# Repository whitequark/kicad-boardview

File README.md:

# KiCad to Boardview exporter

The _KiCad to Boardview exporter_ reads KiCad PCB layout files and writes _Boardview_ files. _Boardview_ is a set of file formats used in the industry for communicating important data about PCB in post-production stage, such as component, pin, and test point placement.

The _Boardview_ file formats do not typically have a specification or even a name. The _KiCad to Boardview_ exporter writes ".brd" files with ASCII _Boardview_ data. These files can be opened with MIT-licensed [OpenBoardView][].

[openboardview]: https://openboardview.org/

## Prerequisites

_KiCad to Boardview exporter_ uses the [pcbnew plugin interface][pcbplugin]. It requires KiCad 6 or later. It requires Python with KiCad libraries installed in the Python search path.

[pcbplugin]: https://dev-docs.kicad.org/en/apis-and-binding/pcbnew/

## Usage

Run the exporter as follows:

    ./pcbnew2boardview.py example/example.kicad_pcb example/example.brd

This will read the PCB layout from `example/example.kicad_pcb` and write it to `example/example.brd`.

## Examples

The _Boardview_ file for [Glasgow][] visualized with OpenBoardView looks like this, with the I2C SDA net selected:

For comparison, the PCB layout looks like this:

[glasgow]: https://github.com/whitequark/Glasgow

## Caveats

  * If the pin numbering on KiCad modules does not start with pin 1 and continue consecutively until last pin with an integer name, the pin numbering on the boardview will be wrong.
  * Similarly to the previous caveat, the format does not allow to represent pin names such as `PAD` (on QFN packages) or `A0` (on BGA packages) correctly. These will be assigned arbitrary (but consistent) numbers instead.
  * There is an unknown field in the ".brd" files, written as `0`. It is ignored by OpenBoardView, but might actually mean something.

## License

_KiCad to Boardview exporter_ is distributed under the terms of 0-clause BSD license.

See [LICENSE-0BSD](LICENSE-0BSD.txt) for details.

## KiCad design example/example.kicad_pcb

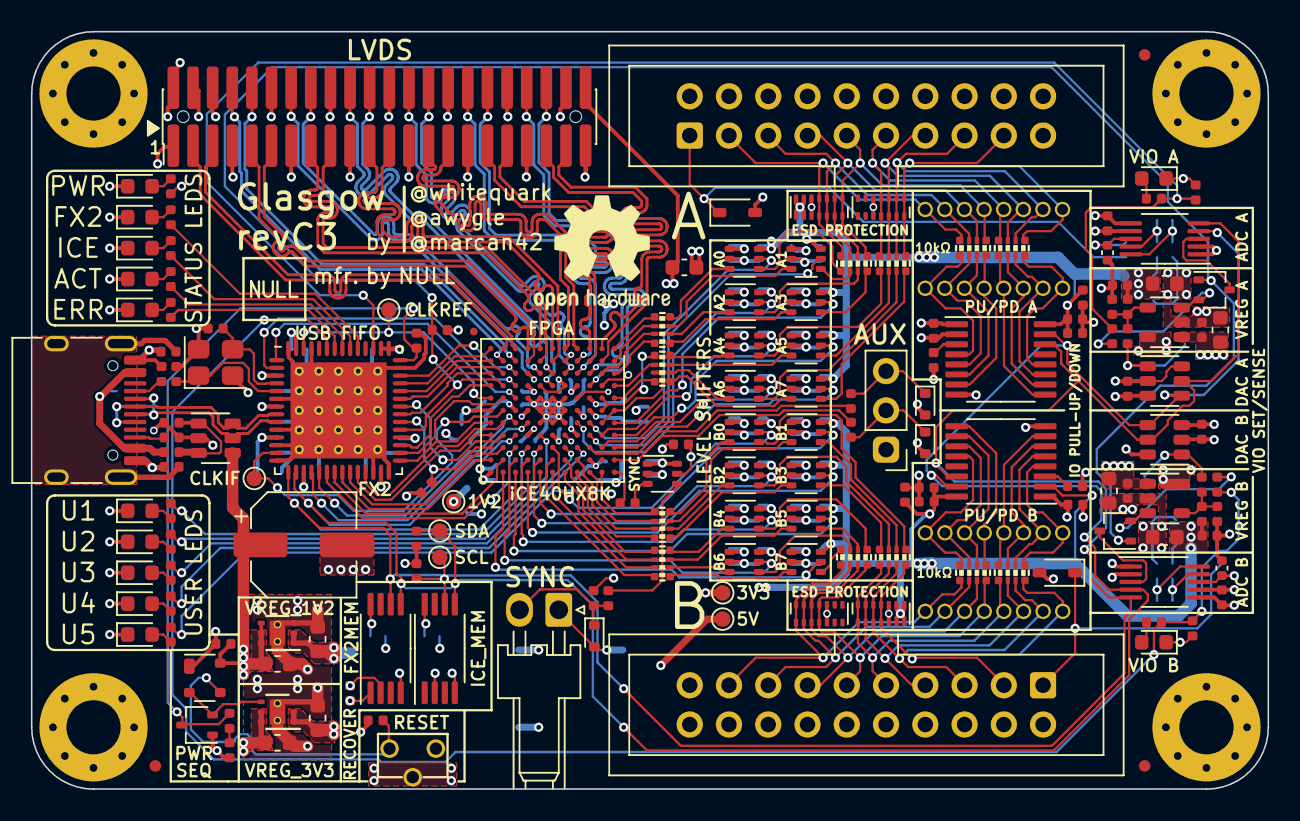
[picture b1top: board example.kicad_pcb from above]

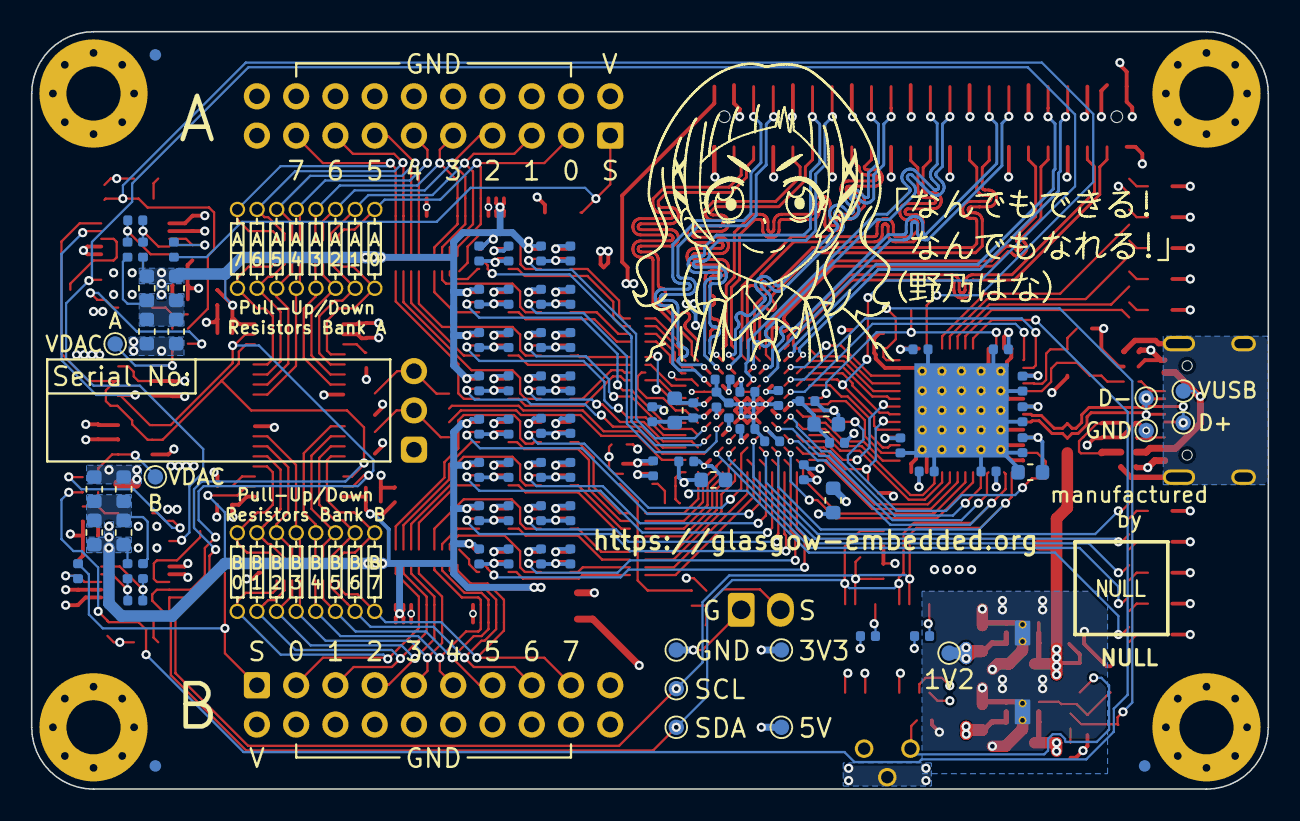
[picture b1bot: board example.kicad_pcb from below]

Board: 4 copper layers, 80.0 x 49.0 mm, 265 parts (93 on the bottom side), 226 nets.

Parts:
C1, C14, C19, C26, C27, C28, C31, C53, C76, C80, C82, C83, C86, C92: 4u7; C_0603_1608Metric
C2, C3, C4, C5, C6, C7, C8, C9, C10, C13, C15, C16, C17, C18, C20, C21, C22, C23, C24, C25, C29, C30, C32, C33, C34, C35, C36, C37, C38, C39, C40, C41, C42, C43, C44, C45, C46, C47, C48, C49, C50, C51, C52, C54, C55, C56, C57, C58, C59, C60, C61, C62, C63, C64, C65, C66, C67, C68, C69, C70, C71, C72, C73, C74, C75, C77, C78, C79, C81, C84, C85, C88, C89: u1; C_0402_1005Metric
C11, C12: 9p; C_0402_1005Metric
C87: 150u; CP_Elec_6.3x5.9
C90, C91: 1n 50V C0G; C_0402_1005Metric
D1, D14, D15: GRN; LED_0603_1608Metric
D2, D8: WHT; LED_0603_1608Metric
D3, D6, D10: BLU; LED_0603_1608Metric
D4: ORA; LED_0603_1608Metric
D5: RED; LED_0603_1608Metric
D7, D9: PNK; LED_0603_1608Metric
D11, D12, D13: ESD5Z5.0T1G; D_SOD-523
D16, D17: CDSOD323-T36S; D_SOD-323
D18, D19: BAT54CW; SOT-323_SC-70
D20, D21, D22, D23: SP3012-06UTG; UDFN-14_3.5x1.35mm_P0.5mm
D24: BAT54AW; SOT-323_SC-70
FB1: 600R, 0.5A; L_0402_1005Metric
FID1, FID2, FID3, FID4, FID5, FID6: Fiducial_0.75mm_Mask1.5mm
FID8: Fiducial_0.5mm_Dia_1mm_Outer
J1: USB_C_USB2.0; USB_C_Receptacle_HRO_TYPE-C-31-M-12
J2, J3: IDC-Header_2x10_P2.54mm; IDC-Header_2x10_P2.54mm_Vertical
J4: Conn_01x02; Molex_KK-254_1x02_P2.54mm_Horizontal
J5: PinHeader_2x22_P1.27mm; PinHeader_2x22_P1.27mm_Vertical__SMD
J6, J7, J8, J9: Conn_01x08; PinSocket_1x08_P1.27mm_Vertical_DNP
J10: AUX; PinHeader_1x03_P2.54mm_Vertical
MK1, MK2, MK3, MK4: Mounting_Hole_PAD; MountingHole_3.5mm_Pad_Via_CrtYd
NONO_HANA: MECHOKKU; nono_hana_lines
R1, R2, R10, R11, R13, R14, R20, R21, R22, R23, R41, R42, R57, R58: 2k2; R_0402_1005Metric
R3, R4, R5, R9, R17: 100k; R_0402_1005Metric
R6, R8, R50, R51: DNP; R_0603_1608Metric_DNP
R7, R56: 0R33; R_0603_1608Metric
R12, R18, R19, R26, R36, R37, R44, R55: 10k; R_0402_1005Metric
R15, R16: 1k; R_0402_1005Metric
R24, R25, R30, R54: 4R7; R_0402_1005Metric
R27, R33: 49k9; R_0402_1005Metric
R28, R34: 59k; R_0402_1005Metric
R29, R35: 24k3; R_0402_1005Metric
R31, R32: 100R; R_0402_1005Metric
R38, R39, R43, R45: 47R; R_0402_1005Metric
R40: DNP; R_0402_1005Metric_DNP
R46, R47: 20k; R_0402_1005Metric
R48, R49: 0R15; R_0603_1608Metric
R52, R53: 5k1; R_0402_1005Metric
R59, R60: 470; R_0402_1005Metric
RN1, RN2, RN3, RN4, RN7, RN8, RN9, RN10: 33R; R_Array_Convex_4x0402
RN5, RN6, RN11, RN12: 10k; R_Array_Convex_4x0402
SW1: RST; SW_Tactile_SPST_Angled_TC-1109DE
TP1, TP8: 5V; TestPoint_Pad_D1.0mm
TP2, TP17: 1V2; TestPoint_Pad_D1.0mm
TP3, TP7, TP9: 3V3; TestPoint_Pad_D1.0mm
TP4, TP10: SDA; TestPoint_Pad_D1.0mm
TP5, TP11: SCL; TestPoint_Pad_D1.0mm
TP6: CLKREF; TestPoint_Pad_D1.0mm
TP12: GND; TestPoint_Pad_D1.0mm
TP13: VBUS; TestPoint_Pad_D1.0mm
TP14: USBGND; TestPoint_Pad_D1.0mm
TP15: USBDP; TestPoint_Pad_D1.0mm
TP16: USBDM; TestPoint_Pad_D1.0mm
TP18, TP19: VDAC; TestPoint_Pad_D1.0mm
U1: CY7C68013A-56LTX; Cypress_QFN-56-1EP_8x8mm_P0.5mm_EP6.22x6.22mm_ThermalVias
U2: CAT24M01X; TSSOP-8_4.4x3mm_P0.65mm
U3: BL24C256A-SFRC; TSSOP-8_4.4x3mm_P0.65mm
U4, U6, U9, U10, U11, U16, U17, U18, U22, U23, U24, U25, U26, U27, U28, U29, U32: SN74LVC1T45DCKR; SOT-363_SC-70-6
U5, U19: PCA6408APW; TSSOP-16_4.4x5mm_P0.65mm
U7: APX811-40UG-7; SOT-143
U8: TLV75533PDRVR; DFN-6-1EP_2x2mm_P0.65mm_EP1x1.6mm_ThermalVias
U12, U21: INA233; VSSOP-10_3x3mm_P0.5mm
U13, U20: DAC081C081CIMK; SOT-23-6
U14, U31: TPS73101DBV; SOT-23-5
U15: TPD3S014; SOT-23-6
U30: ICE40HX8K-BG121; BGA-121_9.0x9.0mm_Layout11x11_P0.8mm_Ball0.4mm_Pad0.35mm_NS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
U36: TLV73312PQDRVR; DFN-6-1EP_2x2mm_P0.65mm_EP1x1.6mm_ThermalVias
Y1: 24M; Crystal_SMD_3225-4Pin_3.2x2.5mm

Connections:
+1V2: C14.1, C18.1, C24.1, C25.1, C27.1, C77.1, R31.2, R32.2, TP2.1, TP17.1, U30.D4 (VCC), U30.D8 (VCC), U30.H4 (VCC), U30.H8 (VCC), U36.1 (OUT), U36.2 (NC)
+3V3: C1.1, C2.1, C3.1, C4.1, C5.1, C6.1, C7.1, C9.1, C10.1, C15.1, C17.1, C19.1, C20.1, C21.1, C22.1, C23.1, C28.1, C30.1, C32.1, C34.1, C35.1, C36.1, C37.1, C42.1, C43.1, C47.1, C48.1, C55.1, C56.1, C60.1, C61.1, C62.1, C63.1, C68.1, C69.1, C70.1, C71.1, C81.1, C84.1, C85.1, D24.1, J5.2, R1.2, R2.2, R4.1, R12.1, R17.2, R36.2, R37.2, R40.2, R44.2, TP3.1, TP9.1, U1.3 (AVCC), U1.7 (AVCC), U1.11 (VCC), U1.17 (VCC), U1.27 (VCC), U1.32 (VCC), U1.43 (VCC), U1.44 (WAKEUP), U1.55 (VCC), U2.2 (A1), U2.8 (VCC), U3.1 (A0), U3.8 (VCC), U4.1 (VCCA), U5.1 (VDD_I2C), U6.1 (VCCA), U8.1 (OUT), U8.2 (NC), U9.1 (VCCA), U10.1 (VCCA), U11.1 (VCCA), U12.2 (A0), U12.6 (VS), U13.2 (VA), U16.1 (VCCA), U17.1 (VCCA), U18.1 (VCCA), U19.1 (VDD_I2C), U20.2 (VA), U20.6 (ADR0), U21.6 (VS), U22.1 (VCCA), U23.1 (VCCA), U24.1 (VCCA), U25.1 (VCCA), U26.1 (VCCA), U27.1 (VCCA), U28.1 (VCCA), U29.1 (VCCA), U30.C10 (VPP_2V5), U30.D6 (VCCIO_0), U30.F8 (VCCIO_1), U30.H6 (VCCIO_2), U30.L11 (VCC_SPI), U32.1 (VCCA), U32.6 (VCCB)
+5V: C16.1, C26.2, C31.1, C45.1, C59.1, C82.1, C86.2, C87.1, TP1.1, TP8.1, U7.4 (VCC), U8.5 (NC), U8.6 (IN), U14.1 (IN), U15.4 (OUT), U31.1 (IN), U36.4 (EN), U36.5 (NC), U36.6 (IN)
/A0: U1.37 (PA4/FIOADDR0), U30.K3 (IOB_63)
/A1: U1.38 (PA5/FIOADDR1), U30.L2 (IOB_61)
/CC1: J1.A5 (CC1), R53.2
/CC2: J1.B5 (CC2), R52.2
/CLKIF: TP7.1, U1.13 (IFCLK), U30.K6 (IOB_82_GBIN4)
/CLKREF: TP6.1, U1.54 (CLKOUT), U30.D5 (IOT_212), U30.L5 (IOB_81_GBIN5)
/D0: U1.18 (PB0/FD0), U30.H7 (IOB_87)
/D1: U1.19 (PB1/FD1), U30.J7 (IOB_86)
/D2: U1.20 (PB2/FD2), U30.J9 (IOB_106_SDI)
/D3: U1.21 (PB3/FD3), U30.K10 (IOB_108_SS)
/D4: U1.22 (PB4/FD4), U30.L10 (IOB_107_SCK)
/D5: U1.23 (PB5/FD5), U30.K9 (IOB_105_SDO)
/D6: U1.24 (PB6/FD6), U30.L8 (IOB_103_CBSEL0)
/D7: U1.25 (PB7/FD7), U30.K7 (IOB_89)
/ENVA: R18.1, R47.1, R55.2, U1.45 (PD0/FD8)
/ENVB: R19.1, R26.2, R46.1, U1.51 (PD6/FD14)
/FLAGA: U1.29 (CTL0/FLAGA), U30.L7 (IOB_94)
/FLAGB: U1.30 (CTL1/FLAGB), U30.K5 (IOB_79)
/FLAGC: U1.31 (CTL2/FLAGC), U30.L4 (IOB_72)
/FLAGD: U1.40 (PA7/FLAGD/~SLCS), U30.J3 (IOB_57)
/FPGA_DONE: U1.36 (PA3/WU2), U30.K8 (CDONE)
/GNDPLL0: C76.2, C78.2, U30.L6 (GNDPLL0)
/GNDPLL1: C79.2, C80.2, U30.C5 (GNDPLL1)
/IO_Banks/DA0: U4.5 (DIR), U30.C7 (IOT_191)
/IO_Banks/DA1: U11.5 (DIR), U30.C8 (IOT_179)
/IO_Banks/DA2: U6.5 (DIR), U30.D7 (IOT_181)
/IO_Banks/DA3: U16.5 (DIR), U30.A7 (IOT_192)
/IO_Banks/DA4: U9.5 (DIR), U30.B8 (IOT_177)
/IO_Banks/DA5: U17.5 (DIR), U30.A8 (IOT_190)
/IO_Banks/DA6: U10.5 (DIR), U30.B9 (IOT_174)
/IO_Banks/DA7: U18.5 (DIR), U30.A9 (IOT_178)
/IO_Banks/DB0: U22.5 (DIR), U30.F9 (IOR_137)
/IO_Banks/DB1: U26.5 (DIR), U30.G11 (IOR_129)
/IO_Banks/DB2: U23.5 (DIR), U30.G10 (IOR_120)
/IO_Banks/DB3: U27.5 (DIR), U30.H11 (IOR_119)
/IO_Banks/DB4: U24.5 (DIR), U30.H10 (IOR_116)
/IO_Banks/DB5: U28.5 (DIR), U30.J11 (IOR_114)
/IO_Banks/DB6: U25.5 (DIR), U30.J10 (IOR_117)
/IO_Banks/DB7: U29.5 (DIR), U30.K11 (IOR_115)
/IO_Banks/IO_Buffer_A/ISNS_H: R8.2, R30.1, R49.1, R51.1, R56.2
/IO_Banks/IO_Buffer_A/P0: J9.1, RN11.5 (R4.2), U19.4 (P0)
/IO_Banks/IO_Buffer_A/P1: J9.2, RN11.6 (R3.2), U19.5 (P1)
/IO_Banks/IO_Buffer_A/P2: J9.3, RN11.7 (R2.2), U19.6 (P2)
/IO_Banks/IO_Buffer_A/P3: J9.4, RN11.8 (R1.2), U19.7 (P3)
/IO_Banks/IO_Buffer_A/P4: J9.5, RN12.5 (R4.2), U19.9 (P4)
/IO_Banks/IO_Buffer_A/P5: J9.6, RN12.6 (R3.2), U19.10 (P5)
/IO_Banks/IO_Buffer_A/P6: J9.7, RN12.7 (R2.2), U19.11 (P6)
/IO_Banks/IO_Buffer_A/P7: J9.8, RN12.8 (R1.2), U19.12 (P7)
/IO_Banks/IO_Buffer_A/VDAC: R33.1, TP19.1, U20.1 (VOUT)
/IO_Banks/IO_Buffer_A/VFB: R33.2, R34.1, R35.2, U31.4 (FB)
/IO_Banks/IO_Buffer_A/VIO_EN: D19.2, R55.1, U31.3 (EN)
/IO_Banks/IO_Buffer_A/VSENSE: D17.1 (K), J2.1, R60.2
/IO_Banks/IO_Buffer_A/X0: RN7.8 (R1.2), U4.3 (A)
/IO_Banks/IO_Buffer_A/X1: RN7.7 (R2.2), U11.3 (A)
/IO_Banks/IO_Buffer_A/X2: RN7.6 (R3.2), U6.3 (A)
/IO_Banks/IO_Buffer_A/X3: RN7.5 (R4.2), U16.3 (A)
/IO_Banks/IO_Buffer_A/X4: RN8.8 (R1.2), U9.3 (A)
/IO_Banks/IO_Buffer_A/X5: RN8.7 (R2.2), U17.3 (A)
/IO_Banks/IO_Buffer_A/X6: RN8.6 (R3.2), U10.3 (A)
/IO_Banks/IO_Buffer_A/X7: RN8.5 (R4.2), U18.3 (A)
/IO_Banks/IO_Buffer_A/Y0: RN9.1 (R1.1), U4.4 (B)
/IO_Banks/IO_Buffer_A/Y1: RN9.2 (R2.1), U11.4 (B)
/IO_Banks/IO_Buffer_A/Y2: RN9.3 (R3.1), U6.4 (B)
/IO_Banks/IO_Buffer_A/Y3: RN9.4 (R4.1), U16.4 (B)
/IO_Banks/IO_Buffer_A/Y4: RN10.1 (R1.1), U9.4 (B)
/IO_Banks/IO_Buffer_A/Y5: RN10.2 (R2.1), U17.4 (B)
/IO_Banks/IO_Buffer_A/Y6: RN10.3 (R3.1), U10.4 (B)
/IO_Banks/IO_Buffer_A/Y7: RN10.4 (R4.1), U18.4 (B)
/IO_Banks/IO_Buffer_A/Z0: D22.4 (N/C), D22.11 (Ch4), J2.3, J8.1, RN9.8 (R1.2), RN11.4 (R4.1)
/IO_Banks/IO_Buffer_A/Z1: D22.3 (N/C), D22.12 (Ch3), J2.5, J8.2, RN9.7 (R2.2), RN11.3 (R3.1)
/IO_Banks/IO_Buffer_A/Z2: D22.2 (N/C), D22.13 (Ch2), J2.7, J8.3, RN9.6 (R3.2), RN11.2 (R2.1)
/IO_Banks/IO_Buffer_A/Z3: D22.1 (N/C), D22.14 (Ch1), J2.9, J8.4, RN9.5 (R4.2), RN11.1 (R1.1)
/IO_Banks/IO_Buffer_A/Z4: D23.4 (N/C), D23.11 (Ch4), J2.11, J8.5, RN10.8 (R1.2), RN12.4 (R4.1)
/IO_Banks/IO_Buffer_A/Z5: D23.3 (N/C), D23.12 (Ch3), J2.13, J8.6, RN10.7 (R2.2), RN12.3 (R3.1)
/IO_Banks/IO_Buffer_A/Z6: D23.2 (N/C), D23.13 (Ch2), J2.15, J8.7, RN10.6 (R3.2), RN12.2 (R2.1)
/IO_Banks/IO_Buffer_A/Z7: D23.1 (N/C), D23.14 (Ch1), J2.17, J8.8, RN10.5 (R4.2), RN12.1 (R1.1)
/IO_Banks/IO_Buffer_B/ISNS_H: R6.2, R7.2, R24.1, R48.1, R50.1
/IO_Banks/IO_Buffer_B/P0: J7.1, RN5.5 (R4.2), U5.4 (P0)
/IO_Banks/IO_Buffer_B/P1: J7.2, RN5.6 (R3.2), U5.5 (P1)
/IO_Banks/IO_Buffer_B/P2: J7.3, RN5.7 (R2.2), U5.6 (P2)
/IO_Banks/IO_Buffer_B/P3: J7.4, RN5.8 (R1.2), U5.7 (P3)
/IO_Banks/IO_Buffer_B/P4: J7.5, RN6.5 (R4.2), U5.9 (P4)
/IO_Banks/IO_Buffer_B/P5: J7.6, RN6.6 (R3.2), U5.10 (P5)
/IO_Banks/IO_Buffer_B/P6: J7.7, RN6.7 (R2.2), U5.11 (P6)
/IO_Banks/IO_Buffer_B/P7: J7.8, RN6.8 (R1.2), U5.12 (P7)
/IO_Banks/IO_Buffer_B/VDAC: R27.1, TP18.1, U13.1 (VOUT)
/IO_Banks/IO_Buffer_B/VFB: R27.2, R28.1, R29.2, U14.4 (FB)
/IO_Banks/IO_Buffer_B/VIO_EN: D18.2, R26.1, U14.3 (EN)
/IO_Banks/IO_Buffer_B/VSENSE: D16.1 (K), J3.1, R59.2
/IO_Banks/IO_Buffer_B/X0: RN1.8 (R1.2), U22.3 (A)
/IO_Banks/IO_Buffer_B/X1: RN1.7 (R2.2), U26.3 (A)
/IO_Banks/IO_Buffer_B/X2: RN1.6 (R3.2), U23.3 (A)
/IO_Banks/IO_Buffer_B/X3: RN1.5 (R4.2), U27.3 (A)
/IO_Banks/IO_Buffer_B/X4: RN2.8 (R1.2), U24.3 (A)
/IO_Banks/IO_Buffer_B/X5: RN2.7 (R2.2), U28.3 (A)
/IO_Banks/IO_Buffer_B/X6: RN2.6 (R3.2), U25.3 (A)
/IO_Banks/IO_Buffer_B/X7: RN2.5 (R4.2), U29.3 (A)
/IO_Banks/IO_Buffer_B/Y0: RN3.1 (R1.1), U22.4 (B)
/IO_Banks/IO_Buffer_B/Y1: RN3.2 (R2.1), U26.4 (B)
/IO_Banks/IO_Buffer_B/Y2: RN3.3 (R3.1), U23.4 (B)
/IO_Banks/IO_Buffer_B/Y3: RN3.4 (R4.1), U27.4 (B)
/IO_Banks/IO_Buffer_B/Y4: RN4.1 (R1.1), U24.4 (B)
/IO_Banks/IO_Buffer_B/Y5: RN4.2 (R2.1), U28.4 (B)
/IO_Banks/IO_Buffer_B/Y6: RN4.3 (R3.1), U25.4 (B)
/IO_Banks/IO_Buffer_B/Y7: RN4.4 (R4.1), U29.4 (B)
/IO_Banks/IO_Buffer_B/Z0: D20.4 (N/C), D20.11 (Ch4), J3.3, J6.1, RN3.8 (R1.2), RN5.4 (R4.1)
/IO_Banks/IO_Buffer_B/Z1: D20.3 (N/C), D20.12 (Ch3), J3.5, J6.2, RN3.7 (R2.2), RN5.3 (R3.1)
/IO_Banks/IO_Buffer_B/Z2: D20.2 (N/C), D20.13 (Ch2), J3.7, J6.3, RN3.6 (R3.2), RN5.2 (R2.1)
/IO_Banks/IO_Buffer_B/Z3: D20.1 (N/C), D20.14 (Ch1), J3.9, J6.4, RN3.5 (R4.2), RN5.1 (R1.1)
/IO_Banks/IO_Buffer_B/Z4: D21.4 (N/C), D21.11 (Ch4), J3.11, J6.5, RN4.8 (R1.2), RN6.4 (R4.1)
/IO_Banks/IO_Buffer_B/Z5: D21.3 (N/C), D21.12 (Ch3), J3.13, J6.6, RN4.7 (R2.2), RN6.3 (R3.1)
/IO_Banks/IO_Buffer_B/Z6: D21.2 (N/C), D21.13 (Ch2), J3.15, J6.7, RN4.6 (R3.2), RN6.2 (R2.1)
/IO_Banks/IO_Buffer_B/Z7: D21.1 (N/C), D21.14 (Ch1), J3.17, J6.8, RN4.5 (R4.2), RN6.1 (R1.1)
/IO_Banks/QA0: RN7.1 (R1.1), U30.A1 (IOT_225)
/IO_Banks/QA1: RN7.2 (R2.1), U30.A2 (IOT_222)
/IO_Banks/QA2: RN7.3 (R3.1), U30.B3 (IOT_221)
/IO_Banks/QA3: RN7.4 (R4.1), U30.A3 (IOT_223)
/IO_Banks/QA4: RN8.1 (R1.1), U30.B5 (IOT_208), U30.B6 (IOT_198_GBIN0)
/IO_Banks/QA5: RN8.2 (R2.1), U30.A4 (IOT_211)
/IO_Banks/QA6: RN8.3 (R3.1), U30.A6 (IOT_206), U30.B7 (IOT_197_GBIN1)
/IO_Banks/QA7: RN8.4 (R4.1), U30.A5 (IOT_207)
/IO_Banks/QB0: RN1.1 (R1.1), U30.B11 (IOR_161)
/IO_Banks/QB1: RN1.2 (R2.1), U30.C11 (IOR_160)
/IO_Banks/QB2: RN1.3 (R3.1), U30.D10 (IOR_154)
/IO_Banks/QB3: RN1.4 (R4.1), U30.D11 (IOR_152)
/IO_Banks/QB4: RN2.1 (R1.1), U30.E10 (IOR_141_GBIN2)
/IO_Banks/QB5: RN2.2 (R2.1), U30.E11 (IOR_148)
/IO_Banks/QB6: RN2.3 (R3.1), U30.F11 (IOR_140_GBIN3)
/IO_Banks/QB7: RN2.4 (R4.1), U30.F10 (IOR_136)
/IO_Banks/U1: R11.1, U30.G9 (IOR_128)
/IO_Banks/U2: R20.1, U30.G8 (IOR_118)
/IO_Banks/U3: R21.1, U30.E9 (IOR_144)
/IO_Banks/U4: R22.1, U30.D9 (IOR_147)
/IO_Banks/U5: R23.1, U30.E8 (IOR_146)
/IO_Banks/VIOA: C38.1, C39.1, C40.1, C41.1, C49.1, C50.1, C51.1, C52.1, C54.1, C57.1, C83.1, D22.6 (N/C), D22.7 (N/C), D22.8 (Ch6), D22.9 (Ch5), J2.2, R34.2, R42.2, R49.2, R51.2, R54.1, R58.2, U4.6 (VCCB), U6.6 (VCCB), U9.6 (VCCB), U10.6 (VCCB), U11.6 (VCCB), U16.6 (VCCB), U17.6 (VCCB), U18.6 (VCCB), U19.16 (VDD_P)
/IO_Banks/VIOB: C29.1, C46.1, C53.1, C64.1, C65.1, C66.1, C67.1, C72.1, C73.1, C74.1, C75.1, D20.6 (N/C), D20.7 (N/C), D20.8 (Ch6), D20.9 (Ch5), J3.2, R25.1, R28.2, R41.2, R48.2, R50.2, R57.2, U5.2 (ADDR), U5.16 (VDD_P), U22.6 (VCCB), U23.6 (VCCB), U24.6 (VCCB), U25.6 (VCCB), U26.6 (VCCB), U27.6 (VCCB), U28.6 (VCCB), U29.6 (VCCB)
/IO_Banks/VIO_AUX: C33.1, C92.1, J5.44, U30.E4 (VCCIO_3), U30.G4 (VCCIO_3)
/IO_Banks/Z0_N: J5.41, U30.B2 (IOL_2B)
/IO_Banks/Z0_P: J5.39, U30.B1 (IOL_2A)
/IO_Banks/Z1_N: J5.38, U30.C3 (IOL_4B)
/IO_Banks/Z1_P: J5.40, U30.C4 (IOL_4A)
/IO_Banks/Z2_N: J5.33, U30.C1 (IOL_5B)
/IO_Banks/Z2_P: J5.35, U30.C2 (IOL_5A)
/IO_Banks/Z3_N: J5.29, U30.D1 (IOL_8B)
/IO_Banks/Z3_P: J5.27, U30.E1 (IOL_8A)
/IO_Banks/Z4_N: J5.34, U30.D3 (IOL_9B)
/IO_Banks/Z4_P: J5.32, U30.D2 (IOL_9A)
/IO_Banks/Z5_N: J5.26, U30.E3 (IOL_10B)
/IO_Banks/Z5_P: J5.28, U30.E2 (IOL_10A)
/IO_Banks/Z6_N: J5.23, U30.F2 (IOL_12B)
/IO_Banks/Z6_P: J5.21, U30.F1 (IOL_12A)
/IO_Banks/Z7_N: J5.20, U30.F3 (IOL_13B_GBIN7)
/IO_Banks/Z7_P: J5.22, U30.F4 (IOL_13A)
/IO_Banks/Z8_N: J5.17, U30.G2 (IOL_14B)
/IO_Banks/Z8_P: J5.15, U30.G1 (IOL_14A_GBIN6)
/IO_Banks/Z9_N: J5.14, U30.H3 (IOL_17B)
/IO_Banks/Z9_P: J5.16, U30.G3 (IOL_17A)
/IO_Banks/Z10_N: J5.11, U30.H2 (IOL_18B)
/IO_Banks/Z10_P: J5.9, U30.H1 (IOL_18A)
/IO_Banks/Z11_N: J5.3, U30.K1 (IOL_23B)
/IO_Banks/Z11_P: J5.5, U30.J1 (IOL_23A)
/IO_Banks/Z12_N: J5.10, U30.J2 (IOL_25B)
/IO_Banks/Z12_P: J5.8, U30.K2 (IOL_25A)
/IO_Banks/~SYNC: D11.1 (K), J4.2, R38.1, R44.1
/LED_ACT: R15.1, U1.49 (PD4/FD12)
/LED_CY: R13.1, U1.47 (PD2/FD10)
/LED_ERR: R16.1, U1.50 (PD5/FD13)
/LED_FPGA: R14.1, U1.48 (PD3/FD11)
/OE: U1.35 (PA2/SLOE), U30.L3 (IOB_71)
/PKTEND: U1.39 (PA6/PKTEND), U30.L1 (IOB_56)
/RD: U1.1 (RDY0/SLRD), U30.J5 (IOB_78)
/SCL: R2.1, TP5.1, TP11.1, U1.15 (SCL), U2.6 (SCL), U3.6 (SCL), U5.14 (SCL), U12.5 (SCL), U13.5 (SCL), U19.14 (SCL), U20.5 (SCL), U21.5 (SCL), U30.H9 (IOB_104_CBSEL1)
/SDA: R1.1, TP4.1, TP10.1, U1.16 (SDA), U2.5 (SDA), U3.5 (SDA), U5.15 (SDA), U12.4 (SDA), U13.4 (SDA), U19.15 (SDA), U20.4 (SDA), U21.4 (SDA), U30.J8 (IOB_91)
/SHLD: C13.1, J1.S1 (SHIELD), R3.1
/USB_N: J1.A7 (D-), J1.B7 (D-), TP16.1, U1.9 (D-), U15.5 (D1)
/USB_P: J1.A6 (D+), J1.B6 (D+), TP15.1, U1.8 (D+), U15.6 (D2)
/VCCPLL0: C76.1, C78.1, R31.1, U30.J6 (VCCPLL0)
/VCCPLL1: C79.1, C80.1, R32.1, U30.C6 (VCCPLL1)
/VUSB: C8.1, FB1.2, U15.1 (EN), U15.3 (IN)
/WR: U1.2 (RDY1/SLWR), U30.J4 (IOB_64)
/XTALIN: C12.1, U1.5 (XTALIN), Y1.1
/XTALOUT: C11.1, U1.4 (XTALOUT), Y1.3
/xVBUS: FB1.1, J1.A4 (VBUS), J1.A9 (VBUS), J1.B4 (VBUS), J1.B9 (VBUS), TP13.1
/~ALERT: D18.1, D19.1, R17.1, U1.33 (PA0/~INT0), U30.K4 (IOB_73)
/~CY_RESET: C88.1, D24.3, R5.2, U1.42 (~RESET)
/~FPGA_RESET: R9.2, U1.34 (PA1/~INT1), U30.L9 (~CRESET)
/~MR: C89.1, SW1.2, U7.3 (~MR)
GND: C1.2, C2.2, C3.2, C4.2, C5.2, C6.2, C7.2, C8.2, C9.2, C10.2, C11.2, C12.2, C13.2, C14.2, C15.2, C16.2, C17.2, C18.2, C19.2, C20.2, C21.2, C22.2, C23.2, C24.2, C25.2, C26.1, C27.2, C28.2, C29.2, C30.2, C31.2, C32.2, C33.2, C34.2, C35.2, C36.2, C37.2, C38.2, C39.2, C40.2, C41.2, C42.2, C43.2, C45.2, C46.2, C47.2, C48.2, C49.2, C50.2, C51.2, C52.2, C53.2, C54.2, C55.2, C56.2, C57.2, C59.2, C60.2, C61.2, C62.2, C63.2, C64.2, C65.2, C66.2, C67.2, C68.2, C69.2, C70.2, C71.2, C72.2, C73.2, C74.2, C75.2, C77.2, C81.2, C82.2, C83.2, C84.2, C85.2, C86.1, C87.2, C88.2, C89.2, C90.1, C91.1, C92.2, D1.1 (K), D2.1 (K), D3.1 (K), D4.1 (K), D5.1 (K), D6.1 (K), D7.1 (K), D8.1 (K), D9.1 (K), D10.1 (K), D11.2 (A), D12.2 (A), D13.2 (A), D14.1 (K), D15.1 (K), D16.2 (A), D17.2 (A), D20.5 (N/C), D20.10 (GND), D21.5 (N/C), D21.10 (GND), D22.5 (N/C), D22.10 (GND), D23.5 (N/C), D23.10 (GND), J1.A1 (GND), J1.A12 (GND), J1.B1 (GND), J1.B12 (GND), J2.4, J2.6, J2.8, J2.10, J2.12, J2.14, J2.16, J2.18, J3.4, J3.6, J3.8, J3.10, J3.12, J3.14, J3.16, J3.18, J4.1, J5.1, J5.4, J5.6, J5.7, J5.12, J5.13, J5.18, J5.19, J5.24, J5.25, J5.30, J5.31, J5.36, J5.37, J5.42, J5.43, J10.1, MK1.1, MK2.1, MK3.1, MK4.1, R3.2, R9.1, R10.2, R18.2, R19.2, R29.1, R35.1, R41.1, R42.1, R52.1, R53.1, R57.1, R58.1, SW1.1, TP12.1, TP14.1, U1.6 (AGND), U1.10 (AGND), U1.12 (GND), U1.14 (RESERVED), U1.26 (GND), U1.28 (GND), U1.41 (GND), U1.53 (GND), U1.56 (GND), U1.57 (EP), U2.4 (GND), U3.4 (GND), U4.2 (GND), U5.8 (GND), U6.2 (GND), U7.1 (GND), U8.3 (GND), U8.7 (GND), U9.2 (GND), U10.2 (GND), U11.2 (GND), U12.1 (A1), U12.7 (GND), U13.3 (GND), U13.6 (ADR0), U14.2 (GND), U15.2 (GND), U16.2 (GND), U17.2 (GND), U18.2 (GND), U19.2 (ADDR), U19.8 (GND), U20.3 (GND), U21.1 (A1), U21.2 (A0), U21.7 (GND), U22.2 (GND), U23.2 (GND), U24.2 (GND), U25.2 (GND), U26.2 (GND), U27.2 (GND), U28.2 (GND), U29.2 (GND), U30.E5 (GND), U30.E6 (GND), U30.E7 (GND), U30.F5 (GND), U30.F6 (GND), U30.F7 (GND), U30.G5 (GND), U30.G6 (GND), U30.G7 (GND), U30.H5 (GND), U31.2 (GND), U32.2 (GND), U36.3 (GND), U36.7 (GND), Y1.2, Y1.4
unnamed: D1.2 (A), R12.2
unnamed: D2.2 (A), R13.2
unnamed: D3.2 (A), R14.2
unnamed: D4.2 (A), R15.2
unnamed: D5.2 (A), R16.2
unnamed: D6.2 (A), R11.2
unnamed: D7.2 (A), R20.2
unnamed: D8.2 (A), R21.2
unnamed: D9.2 (A), R22.2
unnamed: D10.2 (A), R23.2
unnamed: D12.1 (K), J10.2, R39.1
unnamed: D13.1 (K), J10.3, R43.1
unnamed: D14.2 (A), R46.2
unnamed: D15.2 (A), R47.2
unnamed: R4.2, R5.1
unnamed: R40.1, U3.2 (A1)
unnamed: R36.1, U5.3 (~RESET)
unnamed: D24.2, U7.2 (~RESET), U8.4 (EN)
unnamed: C90.2, R59.1, U12.8 (Vbus)
unnamed: C44.2, R24.2, U12.10 (Vin+)
unnamed: C44.1, R25.2, U12.9 (Vin-)
unnamed: D18.3, U12.3 (~Alert)
unnamed: R6.1, R7.1, U14.5 (OUT)
unnamed: R37.1, U19.3 (~RESET)
unnamed: C91.2, R60.1, U21.8 (Vbus)
unnamed: C58.2, R30.2, U21.10 (Vin+)
unnamed: C58.1, R54.2, U21.9 (Vin-)
unnamed: D19.3, U21.3 (~Alert)
unnamed: R45.2, U30.A11 (IOT_168)
unnamed: R39.2, U30.A10 (IOT_170)
unnamed: R43.2, U30.C9 (IOT_172)
unnamed: R10.1, U30.B4 (IOT_219), U32.5 (DIR)
unnamed: R8.1, R56.1, U31.5 (OUT)
unnamed: R45.1, U32.3 (A)
unnamed: R38.2, U32.4 (B)

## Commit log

2018-11-04 Initial commit.
2018-11-04 Fix pin numbering... mostly.
2018-11-04 Export testpoints as NAILS, too.
2018-12-09 Register as a Pcbnew plugin.
2019-06-17 Remove Python version from shebang.
    Fixes #2.
2020-02-09 Fix relative import in __init__.py
    This commit makes it possible to actually use the plugin as a Python
    module. Previously, Python would try to find pcbnew2boardview in the
    globally installed modules instead of using the local
    pcbnew2boardview.py file.
2020-02-09 Wrap long README.md lines
    This commit makes all README.md lines (except links) fit in 80 Unicode
    characters limit.
2020-02-09 Remove the Python 2 requirement
    The plugin works well with Python 3.
2022-02-04 Make KiCad 6 compatible
2022-02-04 Update for KiCad 6.
2022-02-04 Update README.
2022-05-22 README: Fix pcbplugin docs link
2024-02-26 Add files via upload
    Fix issue #11
2024-02-27 Add files via upload
    Whitespace parity with `main`
2024-02-27 Add files via upload
    Removed extra line at the bottom.
2024-02-27 Fix output being mirrored around X axis in KiCad v6+.
    Fixes #11.
2024-02-27 README: KiCAD → KiCad.
2024-02-29 Update README.md
    Updated dead link for the pcbnew plugin interface.
2024-02-29 Add files via upload
    Updated pad.IsFlipped() command for compatibility with KiCad 8.
2024-02-29 Update README.md
    Fixed dead pcbnew plugin interface link
2024-03-01 Update to be compatible with KiCad 8.
2024-03-03 Add files via upload
    Updated to the current version of Glasgow.
2024-03-03 Delete example directory
    Overwriting did not seem to work.
2024-03-03 Add files via upload
    Updated to the current version of Glasgow (try 2).
2024-03-03 Add files via upload
    Corrected the skip_module function.
2024-03-03 Add files via upload
    Used higher resolution .png files.
2024-03-03 Add files via upload
    Made a less awkward/verbose check for 0 pads in the skip_module function.
2024-03-04 Revert "Add files via upload"
    This reverts commit a51e5d64fdadc1a33a2cb453ce1ee0cdc1b69d23.
2024-03-04 Revert "Add files via upload"
    This reverts commit 1dce2efe442bc507218beb59737010f6dba8fc36.
2024-03-04 Revert "Add files via upload"
    This reverts commit f7a083a97669844b9cff381413e31cc5c728bf85.
2024-03-04 Revert "Add files via upload"
    This reverts commit a2579f0ea6ca0d1cce1b0be929bab1e104a1124e.
2024-03-04 Revert "Delete example directory"
    This reverts commit 596a3d952376cbca4ce76a67b10d3f6667f3ad10.
2024-03-04 Revert "Add files via upload"
    This reverts commit 0c712be9a306c6d0f1b8a2063bd4b359c656085a.
2024-03-04 Add files via upload
    Fixed skip_module function.
2024-03-04 Add files via upload
    Corrected pcbnew2boardview function (accidentally published a blank version).
2024-03-04 Skip all modlules which have no pads, not just REF** ones.
2024-03-05 Update example to Glasgow revC3.
2024-03-20 Add files via upload
    Rewrote pad_sort_key to account for alphanumeric pads.
2024-03-20 Rewrite `pad_sort_key` to account for alphanumeric pads.
2024-03-20 Add files via upload
    Implemented natural_sort_key fix from https://github.com/whitequark/kicad-boardview/pull/17#discussion_r1532876796
2024-03-20 Account for blank pin names
    This commit places blank pin names (NCs, NPTH, etc.) at the end of the sort so that they are not mistakenly pin 1.
2024-03-20 Fix the natural sort function.
2024-03-20 Updated script to be able to output BVR boardviews
    The brd format has some caveats with pin numbers that are detailed in the README. The BVR format does not have these caveats, so I updated the script to also be able to output BVR boardviews.
2024-03-28 Simplified BVR outline drawing
    Rewrote the BVR outline functionality so that it is all self-contained and much simpler (OUTLINE_POINTS vs. OUTLINE_SEGMENTED).
2024-03-29 Declared board variable, fixed spacing
    Declared a board variable for the argument parser and made the spacing in the BVR outline more readable.
2024-07-27 Add support for BVR boardview output
    The BVR format does not have issues with pin numbering.
2025-02-09 Added OpenBoardData file generation
    Added support for generation of OpenBoardData files. OpenBoardData is an open text-based file format that allows boardview files to show important information such as component values and footprints.
